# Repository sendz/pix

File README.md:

# Pix
A simple macropad with screen and rotary encoder

[Acrylic Case file](https://github.com/sendz/keyboard-case/tree/master/Acrylic/Pix)

inspired by Pikatea Monitor Mounted macropad

## License

This design may be reproduced, modified, and manufactured for **Personal Use Only** and not for **Public Sale**, however I allow to anyone who want to do small GB for their community for maximum of 10 pieces of this PCB per group buy.

)

This work is licensed under a [Creative Commons Attribution-NonCommercial 4.0 International License](http://creativecommons.org/licenses/by-nc/4.0/).

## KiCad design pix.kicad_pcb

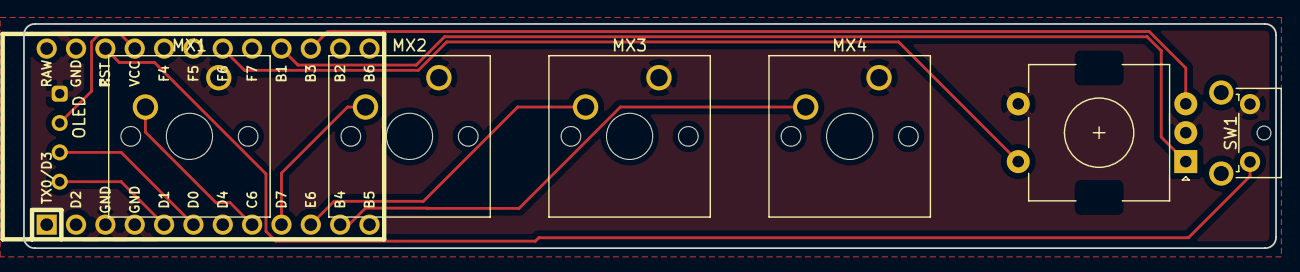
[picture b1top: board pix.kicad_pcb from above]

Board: 2 copper layers, 108.4 x 19.4 mm, 8 parts (0 on the bottom side), 12 nets.

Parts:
MX1, MX2, MX3, MX4: MX-NoLED; SW_Cherry_MX_1.00u_PCB
OL1: OLED; OLED_v2
SW1: SW_PUSH; SW_Tactile_SPST_Angled_MJTP1117
SW2: Rotary_Encoder_Switch; RotaryEncoder_EC11
U1: ProMicro; ArduinoProMicro

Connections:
ENCODER_A: SW2.A, U1.16
ENCODER_B: SW2.B, U1.15
GND: MX1.1, MX2.1, MX3.1, MX4.1, OL1.4, SW1.1, SW2.C, SW2.S1, U1.3, U1.4, U1.23
RESET: SW1.2, U1.22
SCL: OL1.2, U1.6
SDA: OL1.1, U1.5
SWITCH_1: MX1.2, U1.8
SWITCH_2: MX2.2, U1.9
SWITCH_3: MX3.2, U1.10
SWITCH_4: MX4.2, U1.11
SWITCH_5: SW2.S2, U1.18
VCC: OL1.3, U1.21

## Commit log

2020-11-07 Add kicad files
2020-11-07 Add gerbers
2020-12-11 Add Image and Case URL
2021-02-26 Add Firmware directory
2021-02-26 Add firmware
